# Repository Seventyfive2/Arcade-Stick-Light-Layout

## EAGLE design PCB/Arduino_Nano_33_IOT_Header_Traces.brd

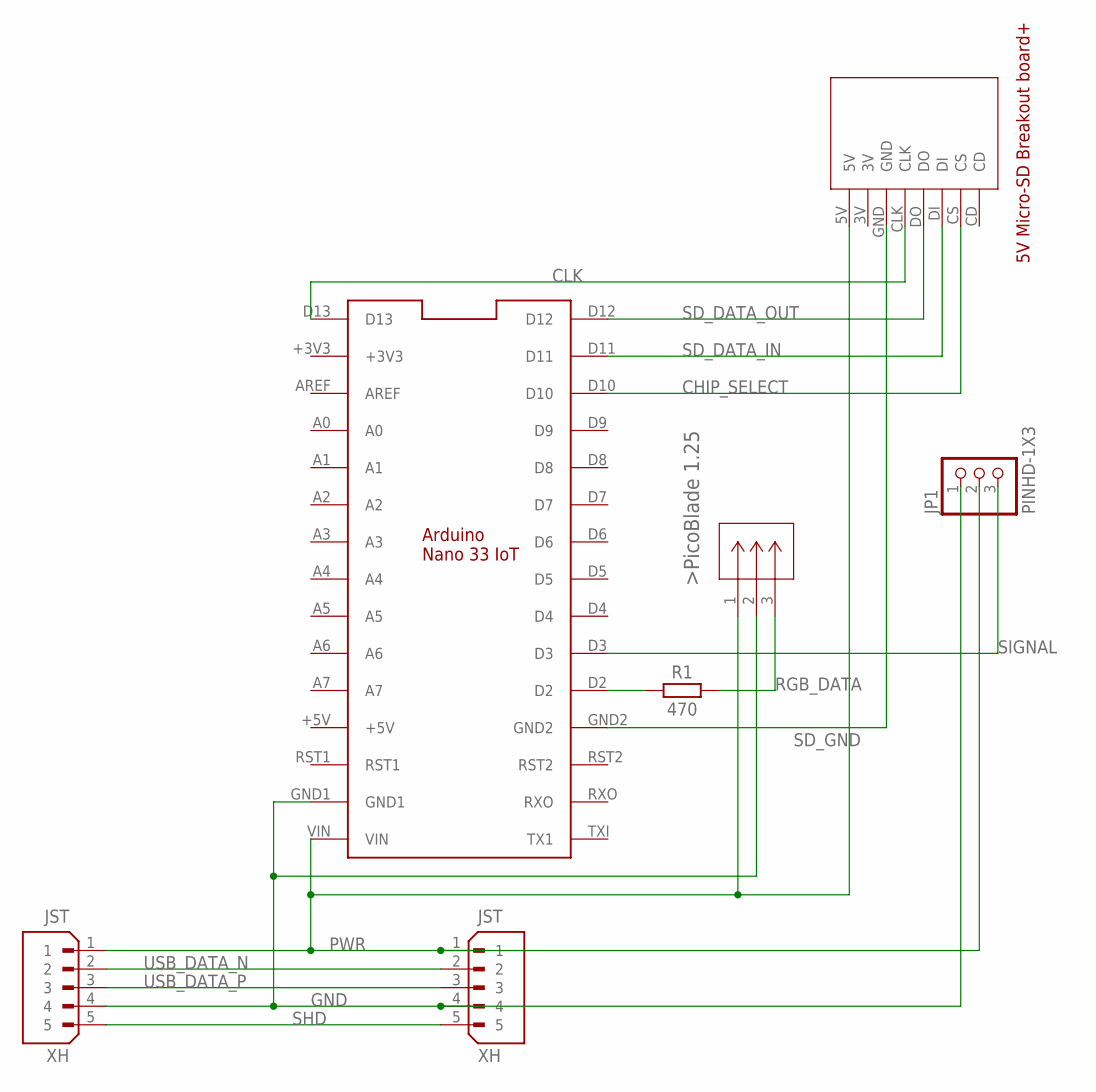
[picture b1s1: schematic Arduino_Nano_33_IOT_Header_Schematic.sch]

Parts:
HEADER2PCB: B5B-XH-A; JST_B5B-XH-A
J1: PICOBLADE_1.25_3-PINCONN03_530470310_MOL; PICOBLADE_1.25_3-PIN
JP1: PINHD-1X3; 1X03
MICROSD_HEADER: MICROSDCARDBREAKOUTBOARD+HEADER; 5V_MICRO-SD_BREAKOUT+_HEADERS
R1: 470; RESAD724W46L381D178B
U$2: ARDUINO_NANOHEADERS; NANO_33_IOT_HEADER
USBCONNECT: B5B-XH-A; JST_B5B-XH-A

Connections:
CHIP_SELECT: MICROSD_HEADER.CS, U$2.D10
CLK: MICROSD_HEADER.CLK, U$2.D13
GND: HEADER2PCB.4, J1.2, JP1.1, U$2.GND1, USBCONNECT.4
unnamed: R1.1, U$2.D2
PWR: HEADER2PCB.1, J1.1, JP1.2, MICROSD_HEADER.5V, U$2.VIN, USBCONNECT.1
RGB_DATA: J1.3, R1.2
SD_DATA_IN: MICROSD_HEADER.DI, U$2.D11
SD_DATA_OUT: MICROSD_HEADER.DO, U$2.D12
SD_GND: MICROSD_HEADER.GND, U$2.GND2
SHD: HEADER2PCB.5, USBCONNECT.5
SIGNAL: JP1.3, U$2.D3
USB_DATA_N: HEADER2PCB.2, USBCONNECT.2
USB_DATA_P: HEADER2PCB.3, USBCONNECT.3

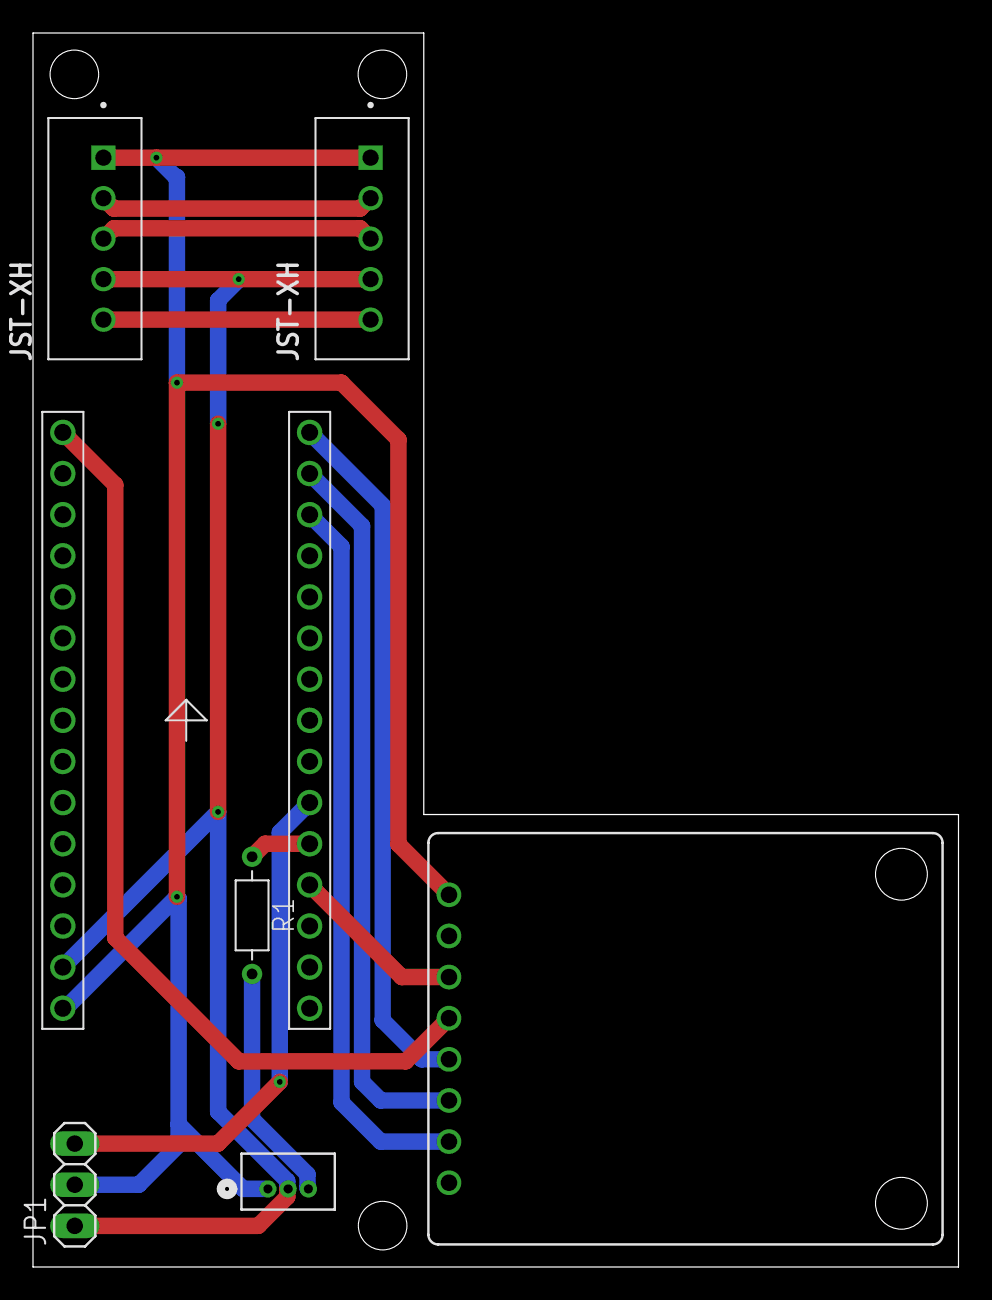
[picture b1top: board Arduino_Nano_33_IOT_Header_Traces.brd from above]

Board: 2 copper layers, 57.1 x 76.2 mm, 7 parts (0 on the bottom side), 13 nets.

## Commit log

2026-01-17 Code Push
    Code for the Arduino, Webpage, and Android App.
2026-01-17 Header PCB Files
2026-01-17 Renamed the Webpage folder
    Renamed for folder name consistency

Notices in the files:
parts and their libraries:
Custom Library: COPYRIGHT: Copyright (C) 2025 Ultra Librarian. All rights reserved.
